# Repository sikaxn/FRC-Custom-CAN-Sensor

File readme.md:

## IronMaple ESP32‐FRC‐devkit sponsored by JLCPCB

If you are looking for IronMaple ESP32‐FRC‐devkit resources, please switch branch to dev-board.

Code, CAD models: https://github.com/sikaxn/FRC-Custom-CAN-Sensor/tree/dev-board/pcb

Manual: https://github.com/sikaxn/FRC-Custom-CAN-Sensor/wiki/800.-IronMaple-ESP32%E2%80%90FRC%E2%80%90devkit-Manual

Design file: https://oshwlab.com/sikaxn/seal-v2-dev-board

Factory test code: https://studenttechsupport.com/customcanespfw/factory/

## Firmware tbd fix

### Addressable LED

1. Allow change number of pixel over CAN **DONE**
2. offline detection on roborio driver **DONE**

### Battery Tracking

1. Indicator Task that use IM dev board RGB LED **DONE**
2. Better CAN protocol - Allow writing energy form roboRIO by user **DONE**
3. Better CAN protocol - Allow user to trigger tag rescan over CAN **DONE**
4. Better CAN protocol - More status feedback from ESP32 (tag write error) **DONE**
5. Better CAN protocol - Empty message upon startup **DONE**
6. Allow change CAN Device Number using web tool **DONE**
7. APP improvment - init new serial number follow BEST protocol (or disable this in setting)
8. APP improvment - App should not be set as default NFC app on Android

### IM ESP Devkit demo 

1. Bugfix - Change CAN Device Number using web tool currently not working. **DONE**
2. Maybe merge Addressable LED with it.

### Battery Tracking + addressable LED combined firmware

1. New firmware that combine those two together. **DONE**

# Custom CAN sensor with roboRIO

Please also check out the WiKi section for more documentation!

https://github.com/sikaxn/FRC-Custom-CAN-Sensor/wiki

# Some resources in another branch

This repo need some cleanup. Will do later.

https://github.com/sikaxn/FRC-Custom-CAN-Sensor/tree/dev-board

## IronMaple ESP32‐FRC‐devkit sponsored by JLCPCB

If you are looking for IronMaple ESP32‐FRC‐devkit resources, please switch branch to dev-board.

Code, CAD models: https://github.com/sikaxn/FRC-Custom-CAN-Sensor/tree/dev-board/pcb

Manual: https://github.com/sikaxn/FRC-Custom-CAN-Sensor/wiki/800.-IronMaple-ESP32%E2%80%90FRC%E2%80%90devkit-Manual

Design file: https://oshwlab.com/sikaxn/seal-v2-dev-board

Factory test code: https://studenttechsupport.com/customcanespfw/factory/

## Web firmware flasher

Pre built ESP32 firmware for Battery RFID Tracker and Addressable LED Controller. Just Chrome, USB and flash.

https://studenttechsupport.com/customcanespfw/

Web flasher source code: https://github.com/sikaxn/sikaxn.github.io/tree/master/customcanespfw

## ChiefDelphi Thread
https://www.chiefdelphi.com/t/custom-can-sensor-some-good-progress/501764

## Video

Potentiometer analog input
https://www.youtube.com/watch?v=bEm6USGRP-E

LED (pin 13) digital output
https://www.youtube.com/shorts/q937u09llhw

roboRIO heartbeat (look at the LED blinking while enabled)
https://www.youtube.com/shorts/c1ieu9o8Lzo

## ⚠️ Disclaimer

This project is **for demo and under work**. Faulty CAN frame could bring entire CAN bus down. 

This project use **AI generated content**. 

---
# What's in this repository:

1. [Arduino Mega] Digital Analog bi-directional ([Docs](Arduino/readme.md) / [Arduino Firmware](Arduino/Digital_Analog/) / [roboRIO](roboRIO/can-test/) / [RIO Simulator](scripts/ADrioSIm.py))
2. [Arduino Mega] REV Colour sensor  ([Docs](Arduino/readme.md) / [Arduino Firmware](Arduino/REVColourSensorV3/) / [roboRIO](roboRIO/can-test/)) (this share the same roboRIO code with the first one)
3. [Arduino Mega] LCD Screen  ([Arduino Firmware](Arduino/LCD/) / [roboRIO](roboRIO/can-LCD/) / [RIO Simulator](scripts/LCDSendRIOSIM.py))
4. **NOT FRC LEGAL** [ESP32] Robomaster motor gateway (dual CAN on ESP32)  ([Arduino Firmware](Arduino/RM_stuff/) / [roboRIO](roboRIO/djimotor/))
5. **NOT FRC LEGAL** Robomaster DT7 Remote on CAN  ([Arduino Firmware](Arduino/RM_stuff/) / [roboRIO](roboRIO/dt7/))
6. [ESP32] Battery Tracking System ([Arduino Firmware](Arduino/Battery_Tracking/batteryReaderAutoPD/) / [roboRIO](roboRIO/batteryReader/) / [Android APP](https://github.com/sikaxn/FRC-RFID-Battery-Reader) / [Docs](Arduino/Battery_Tracking/readme.md))
7. [ESP32] ToF using 4 VL53L1X ([Docs](Arduino/ToF/readme.md) / [Arduino Firmware](Arduino/ToF/laserCANx4/) / [roboRIO](roboRIO/ToF/) / [UITool](scripts/ToFReaderROI.py) / [ROI Calculator Tool](scripts/TofRIOCalc.py))
8. [ESP32] Addressable LED Controller ([Arduino Firmware](Arduino/addressableLED/) / [roboRIO](roboRIO/addressableLED/))
9. [ESP32] Battery Tracking ([Arduino Firmware](Arduino/Battery_Tracking/) / [roboRIO](roboRIO/batteryReaderNew/)) / [Docs](https://github.com/sikaxn/FRC-Custom-CAN-Sensor/wiki/900.-IronMaple-RFID-Battery-Tracking-Solution)
10. [ESP32] Battery Tracking LF ([Arduino Firmware](Arduino/Battery_Tracking_LF/) / [roboRIO](roboRIO/batteryReaderLF/)) / [Docs](Arduino/Battery_Tracking_LF/readme.md)
11. [ESP32] REV and Andymark Colour sensor ([Arduino Firmware](Arduino/REVAMColourSensor/) / [roboRIO](roboRIO/andymarkColourSensor/)) / [Docs](https://github.com/sikaxn/FRC-Custom-CAN-Sensor/wiki/920.-REV---Andymark-Colour-sensor-to-CAN-interface)

---

# Important reminder of ESP32 radio:

Per FRC Game Manual (2025) R707 and E301, Wi-Fi radio should not be used within competition area and Bluetooth radio should not be used if robot is competing on the field. As for now, none of the code utilizing ESP32 have any wireless capability. However, if further update enabled this capability, the use of such device and software should be carefully planned and coordinated to stay in compliance with the game manual. 

---
## How FRC CAN bus works

The 'CAN ID' we talked about when setting up motor controllers (Spark, Kraken, PDP, etc) is a number from 0-63. This is not the CAN identifier (message ID) used in CAN data layer. FRC Use a very specific scheme outlined in FRC CAN specification to convert certain information to CAN identifier. All device connected to roboRIO must follow this scheme when determine what ID to send data to and read form.

https://docs.wpilib.org/en/stable/docs/software/can-devices/can-addressing.html#requirements-for-frc-can-nodes

CAN identifier is calculated from device ID (device type ID), manufacturer ID, API ID (in the documentation it talked about API Class and Index but doesn't matter and it is just a suggestion. Each device will have its unique API ID designed for its use) and device number (0-63 as the traditional 'CAN ID' we talked about in FRC). 

You must generate your CAN identifier (message ID) using this very specific way. A device will have multiple CAN message sent to and from roboRIO (and possibly to other non-roboRIO device). These different messages will share the same device type ID, manufacturer ID and device number. API ID will change based on use. 

---
## Update

1. REVCOlourSensorV3 Arduino sketch has been updated to do conversion in code. In addition, rm_dt7 is added to handle Robomaster / DJI DT7 Remote with DR16. This is not legal to use in FRC. However you could still take a look at these conversion. 

```
// === CAN Constants ===
#define DEVICE_TYPE_ID        0x0A  //DONOT CHANGE
#define MANUFACTURER_ID  0x08  //DONOT CHANGE
#define DEVICE_NUMBER    33  // Device Number 0-63
#define STATUS_API_ID        0x180
#define COLOR_SENSOR_API_ID  0x184
#define CONTROL_API_ID       0x190
#define HEARTBEAT_ID         0x01011840

uint32_t makeCANMsgID(uint8_t deviceID, uint8_t manufacturerID, uint16_t apiID, uint8_t deviceNumber) {
  return ((uint32_t)(deviceID & 0xFF) << 24) |
         ((uint32_t)(manufacturerID & 0xFF) << 16) |
         ((uint32_t)(apiID & 0x3FF) << 6) |
         (deviceNumber & 0x3F);
}
```
2. An ID converter script is added. see below for usage.

3. DO NOT change DEVICE_TYPE_ID and MANUFACTURER_ID as this will result roboRIO code stop working. 

---

---

## **Message ID Generator GUI Tool**

A minimal Tkinter application for converting between FRC 29-bit CAN IDs and their four fields.

## **CANDbg Message Viewer tool**

A minimal Tkinter application viewing CAN messages using python-can.

Support Ctrl + C to copy message and roboRIO heartbeat decoding.

---

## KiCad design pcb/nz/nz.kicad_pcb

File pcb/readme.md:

# IronMaple ESP32-FRC-devkit

Please visit https://oshwlab.com/sikaxn/seal-v2-dev-board

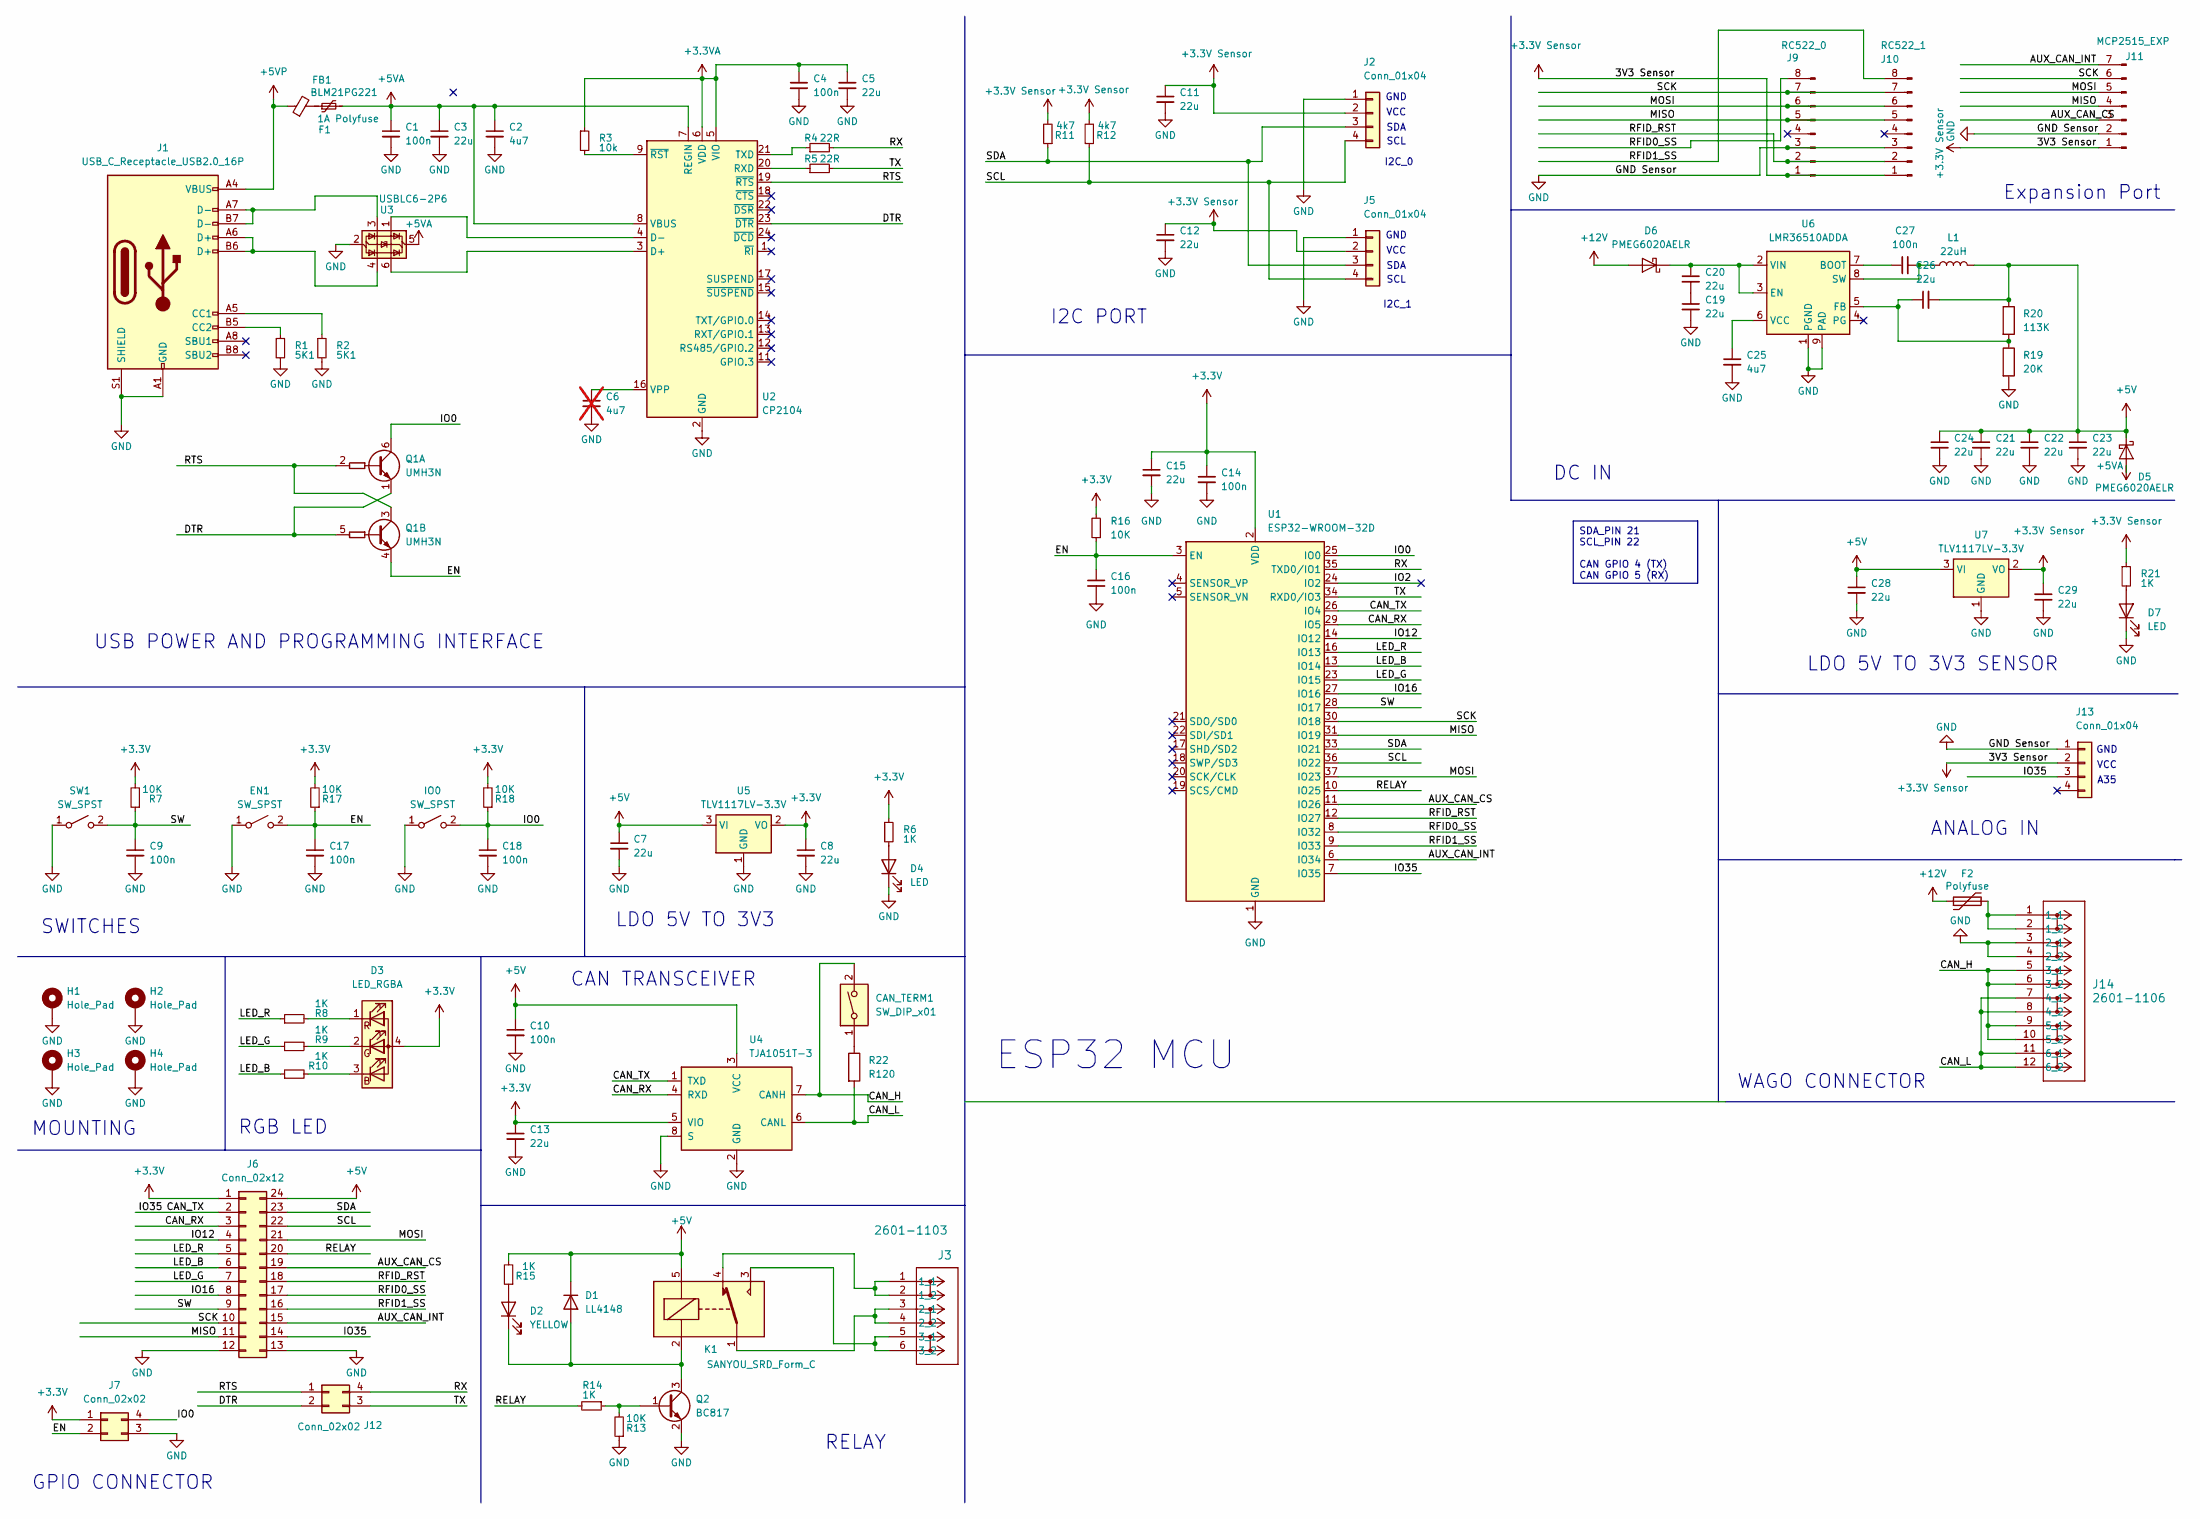
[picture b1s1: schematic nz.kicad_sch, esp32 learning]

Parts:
C1, C4, C9, C10, C14, C16, C17, C18, C27: 100n; C_01005_0402Metric
C2, C25: 4u7; C_01005_0402Metric
C3, C5, C7, C8, C11, C12, C13, C15, C19, C20, C21, C22, C23, C24, C26, C28, C29: 22u; C_01005_0402Metric
C6: 4u7; C_01005_0402Metric; not fitted
CAN_TERM1: SW_DIP_x01; SW_DIP_SPSTx01_Slide_6.7x4.1mm_W6.73mm_P2.54mm_LowProfile_J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
D1: LL4148; D_MiniMELF
D2: YELLOW; LED_0201_0603Metric
D3: LED_RGBA; LED_RGB_Wuerth-PLCC4_3.2x2.8mm_150141M173100
D4, D7: LED; LED_0201_0603Metric
D5, D6: PMEG6020AELR; Nexperia_CFP3_SOD-123W
EN1: SW_SPST; SW_Push_1P1T_NO_6x6mm_H9.5mm
F1: 1A Polyfuse; Fuse_1206_3216Metric_Pad1.42x1.75mm_HandSolder
F2: Polyfuse; Fuse_1206_3216Metric_Pad1.42x1.75mm_HandSolder
FB1: BLM21PG221; L_0603_1608Metric_Pad1.05x0.95mm_HandSolder
H1, H2, H3, H4: Hole_Pad; MountingHole_3.2mm_M3_Pad_Via
IO0: SW_SPST; SW_Push_1P1T_NO_6x6mm_H9.5mm
J1: USB_C_Receptacle_USB2.0_16P; USB_C_Receptacle_HRO_TYPE-C-31-M-12
J2, J5, J13: Conn_01x04; PinHeader_1x04_P1.00mm_Vertical
J3: 2601-1103; CONN3_2601-1103_WAG
J6: Conn_02x12; PinHeader_2x12_P1.00mm_Vertical
J7, J12: Conn_02x02; PinHeader_2x02_P1.00mm_Vertical
J9: RC522_0; PinHeader_1x08_P1.00mm_Vertical
J10: RC522_1; PinHeader_1x08_P1.00mm_Vertical
J11: MCP2515_EXP; PinHeader_1x07_P1.00mm_Vertical
J14: 2601-1106; CONN6_2601-1106_WAG
K1: SANYOU_SRD_Form_C; Relay_SPDT_SANYOU_SRD_Series_Form_C
L1: 22uH; L_1008_2520Metric
Q1: UMH3N; SOT-363_SC-70-6
Q2: BC817; SOT-23
R1, R2: 5K1; R_0402_1005Metric
R3: 10k; R_0402_1005Metric
R4, R5: 22R; R_0402_1005Metric
R6, R8, R9, R10, R14, R15, R21: 1K; R_0402_1005Metric
R7, R13, R16, R17, R18: 10K; R_0402_1005Metric
R11, R12: 4k7; R_0402_1005Metric
R19: 20K; R_0402_1005Metric
R20: 113K; R_0402_1005Metric
R22: R120; R_0402_1005Metric
SW1: SW_SPST; SW_Push_1P1T_NO_6x6mm_H9.5mm
U1: ESP32-WROOM-32D; ESP32-WROOM-32D-3d
U2: CP2104; QFN-24-1EP_4x4mm_P0.5mm_EP2.6x2.6mm
U3: USBLC6-2P6; SOT-666
U4: TJA1051T-3; SOIC-8_3.9x4.9mm_P1.27mm
U5, U7: TLV1117LV-3.3V; SOT-223-3_TabPin2
U6: LMR36510ADDA; Texas_HTSOP-8-1EP_3.9x4.9mm_P1.27mm_EP2.95x4.9mm_Mask2.4x3.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

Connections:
+3.3V: C8.1, C13.1, C14.1, C15.1, D3.4 (A), J6.1, J7.1, R6.1, R7.2, R16.2, R17.2, R18.2, U1.2 (VDD), U4.5 (VIO), U5.2 (VO)
+3.3V Sensor: C11.1, C12.1, C29.1, J2.2, J5.2, J9.1, J10.1, J11.1, J13.2, R11.2, R12.2, R21.1, U7.2 (VO)
+3.3VA: C4.1, C5.1, R3.1, U2.5 (VIO), U2.6 (VDD)
+5V: C7.1, C10.1, C21.1, C22.1, C23.1, C24.1, C26.2, C28.1, D1.1 (K), D5.1 (K), J6.24, K1.5, L1.2, R15.2, R20.1, U4.3 (VCC), U5.3 (VI), U7.3 (VI)
+5VA: C1.1, C2.1, C3.1, D5.2 (A), F1.2, U2.7 (REGIN), U2.8 (VBUS), U3.5 (VBUS)
+5VP: FB1.1, J1.A4 (VBUS), J1.A9 (VBUS), J1.B4 (VBUS), J1.B9 (VBUS)
+12V: D6.2 (A), F2.1
/AUX_CAN_CS: J6.19, J11.3, U1.11 (IO26)
/AUX_CAN_INT: J6.15, J11.7, U1.6 (IO34)
/CAN_H: CAN_TERM1.2, J14.5 (3_1), J14.6 (3_2), J14.9 (5_1), J14.10 (5_2), U4.7 (CANH)
/CAN_L: J14.7 (4_1), J14.8 (4_2), J14.11 (6_1), J14.12 (6_2), R22.2, U4.6 (CANL)
/CAN_RX: J6.3, U1.29 (IO5), U4.4 (RXD)
/CAN_TX: J6.2, J6.14, J13.3, U1.7 (IO35), U1.26 (IO4), U4.1 (TXD)
/DTR: J12.2, Q1.1 (E1), Q1.5 (B2), U2.23 (~DTR)
/EN: C16.1, C17.1, EN1.2 (B), J7.2, Q1.4 (E2), R16.1, R17.1, U1.3 (EN)
/IO0: C18.1, IO0.2 (B), J7.4, Q1.6 (C1), R18.1, U1.25 (IO0)
/IO2: U1.24 (IO2)
/IO12: J6.4, U1.14 (IO12)
/IO16: J6.8, U1.27 (IO16)
/LED_B: J6.6, R10.1, U1.13 (IO14)
/LED_G: J6.7, R9.1, U1.23 (IO15)
/LED_R: J6.5, R8.1, U1.16 (IO13)
/MISO: J6.11, J9.5, J10.5, J11.4, U1.31 (IO19)
/MOSI: J6.21, J9.6, J10.6, J11.5, U1.37 (IO23)
/RELAY: J6.20, R14.2, U1.10 (IO25)
/RFID0_SS: J6.17, J9.8, U1.8 (IO32)
/RFID1_SS: J6.16, J10.8, U1.9 (IO33)
/RFID_RST: J6.18, J9.2, J10.2, U1.12 (IO27)
/RTS: J12.1, Q1.2 (B1), Q1.3 (C2), U2.19 (~RTS)
/RX: J12.4, R4.2, U1.35 (TXD0/IO1)
/SCK: J6.10, J9.7, J10.7, J11.6, U1.30 (IO18)
/SCL: J2.4, J5.4, J6.22, R12.1, U1.36 (IO22)
/SDA: J2.3, J5.3, J6.23, R11.1, U1.33 (IO21)
/SW: C9.1, J6.9, R7.1, SW1.2 (B), U1.28 (IO17)
/TX: J12.3, R5.2, U1.34 (RXD0/IO3)
GND: C1.2, C2.2, C3.2, C4.2, C5.2, C6.2, C7.2, C8.2, C9.2, C10.2, C11.2, C12.2, C13.2, C14.2, C15.2, C16.2, C17.2, C18.2, C19.2, C21.2, C22.2, C23.2, C24.2, C25.2, C28.2, C29.2, D4.1 (K), D7.1 (K), EN1.1 (A), H1.1, H2.1, H3.1, H4.1, IO0.1 (A), J1.A1 (GND), J1.A12 (GND), J1.B1 (GND), J1.B12 (GND), J1.S1 (SHIELD), J2.1, J5.1, J6.12, J6.13, J7.3, J9.3, J10.3, J11.2, J13.1, J14.3 (2_1), J14.4 (2_2), Q2.2 (E), R1.2, R2.2, R13.1, R19.2, SW1.1 (A), U1.1 (GND), U1.15 (GND), U1.38 (GND), U1.39 (GND), U2.2 (GND), U2.25 (GND), U3.2 (GND), U4.2 (GND), U4.8 (S), U5.1 (GND), U6.1 (PGND), U6.9 (PAD), U7.1 (GND)
unnamed: C19.1, C20.2
unnamed: CAN_TERM1.1, R22.1
unnamed: D1.2 (A), D2.1 (K), K1.2, Q2.3 (C)
unnamed: D2.2 (A), R15.1
unnamed: D3.3 (BK), R10.2
unnamed: D3.2 (GK), R9.2
unnamed: D3.1 (RK), R8.2
unnamed: D4.2 (A), R6.2
unnamed: C20.1, D6.1 (K), U6.2 (VIN), U6.3 (EN)
unnamed: D7.2 (A), R21.2
unnamed: F1.1, FB1.2
unnamed: J1.A5 (CC1), R2.1
unnamed: J1.B5 (CC2), R1.1
unnamed: J1.A6 (D+), J1.B6 (D+), U3.4 (I/O2)
unnamed: J1.A7 (D-), J1.B7 (D-), U3.3 (I/O2)
unnamed: J3.1 (1_1), J3.2 (1_2), K1.4
unnamed: J3.3 (2_1), J3.4 (2_2), K1.1
unnamed: J3.5 (3_1), J3.6 (3_2), K1.3
unnamed: F2.2, J14.1 (1_1), J14.2 (1_2)
unnamed: Q2.1 (B), R13.2, R14.1
unnamed: U2.3 (D+), U3.6 (I/O1)
unnamed: U2.4 (D-), U3.1 (I/O1)
unnamed: R5.1, U2.20 (RXD)
unnamed: R4.1, U2.21 (TXD)
unnamed: C6.1, U2.16 (VPP)
unnamed: R3.2, U2.9 (~RST)
unnamed: C27.1, U6.7 (BOOT)
unnamed: C26.1, R19.1, R20.2, U6.5 (FB)
unnamed: C27.2, L1.1, U6.8 (SW)
unnamed: C25.1, U6.6 (VCC)

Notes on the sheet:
SDA_PIN 21 SCL_PIN 22 CAN GPIO 4 (TX) CAN GPIO 5 (RX)
LDO 5V TO 3V3 SENSOR
CAN TRANSCEIVER
RELAY
I2C_1
LDO 5V TO 3V3
GND
VCC
I2C PORT
MOUNTING
ESP32 MCU
RGB LED
A35
WAGO CONNECTOR
GPIO CONNECTOR
I2C_0
ANALOG IN
SDA
DC IN
SWITCHES
USB POWER AND PROGRAMMING INTERFACE
SCL
Expansion Port

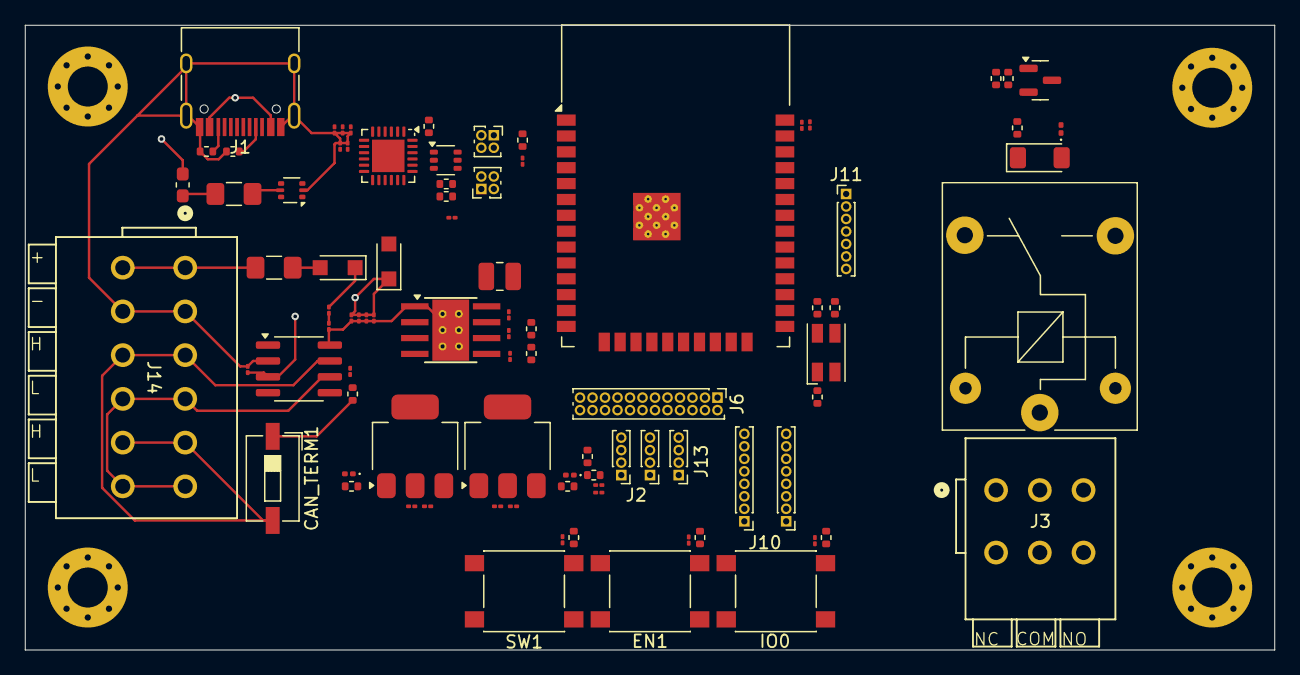
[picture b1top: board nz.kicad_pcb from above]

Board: 6 copper layers, 100.0 x 50.0 mm, 92 parts (0 on the bottom side), 65 nets.

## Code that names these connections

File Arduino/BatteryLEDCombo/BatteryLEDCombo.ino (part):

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// ===============  HARDWARE DEFINITIONS  ============
// ==================================================
#define RST_PIN        22
#define CAN_TX_PIN     GPIO_NUM_4
#define CAN_RX_PIN     GPIO_NUM_5

// RGB LED Pins
#define LED_R 15
#define LED_G 13
#define LED_B 14
#define RELAY_PIN 25
#define LED_TOGGLE_BTN_PIN 17

// Addressable LED Strip
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QueueHandle_t canRxQueue;

void setup() {
  pinMode(LED_R, OUTPUT);
  pinMode(LED_B, OUTPUT);
  pinMode(LED_G, OUTPUT);
  pinMode(RELAY_PIN, OUTPUT);
  digitalWrite(RELAY_PIN, LOW);
  pinMode(LED_TOGGLE_BTN_PIN, INPUT_PULLUP);

  Serial.begin(115200);
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  // === CAN (TWAI) Configuration ===
  twai_general_config_t g_config = {
    .mode = TWAI_MODE_NORMAL,
    .tx_io = CAN_TX_PIN,
    .rx_io = CAN_RX_PIN,
    .clkout_io = TWAI_IO_UNUSED,
    .bus_off_io = TWAI_IO_UNUSED,
    .tx_queue_len = 5,
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  bool lastBtn = digitalRead(0);
  bool lastToggleBtn = digitalRead(LED_TOGGLE_BTN_PIN);
  for (;;) {
    digitalWrite(RELAY_PIN, (localLedEnabled && canOnOff) ? HIGH : LOW);
    bool toggleBtn = digitalRead(LED_TOGGLE_BTN_PIN);
    if (lastToggleBtn == HIGH && toggleBtn == LOW) {
      localLedEnabled = !localLedEnabled;
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
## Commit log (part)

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2025-05-14 init commit
2025-05-14 fixed can RX issue on arduino
2025-05-14 updated doc
2025-05-14 bug fix and have arduino listen roborio heartbeat
2025-05-15 added support for rev colour sensor v3 on arduino
2025-05-16 fix an issue where if it is very bright white colour sensor would disconnect
2025-05-18 ID conversion tool
2025-05-18 id conversion update
2025-05-18 added dt7 decoding
2025-05-23 eeee
2025-05-23 dt7 explain
2025-05-26 add support to dji motor
2025-05-26 improved dji motor api
2025-05-29 add LCD
2025-05-30 add lcd java
2025-05-30 add battery example
2025-05-30 doc update and cleaning folder structure
2025-05-30 make repository cleaner
2025-06-05 api improvement before moving on to CAN
2025-06-06 add roborio lib
2025-06-06 bugfix
2025-06-06 battery manager task added
2025-06-06 docs update
2025-06-06 folder name change
2025-06-06 img update
2025-06-07 now use UTC on json
2025-06-07 utc fix
2025-06-09 reader holder img
2025-06-10 pd auto discovery test
2025-06-11 always use pd voltage first
2025-06-11 energy calculation updated
2025-06-11 comment clean up
2025-06-13 add tof
2025-06-13 uodate readme
2025-06-13 added roi ui tool
2025-06-13 pushing the limit...
2025-06-14 revert some mistake
2025-06-14 ToF Roborio driver started
2025-06-17 added pcb
2025-06-18 ipdate
2025-06-18 (trying) to fix roi
2025-06-18 update roborio driver
2025-06-18 clean up dir
2025-06-18 add ToF readme
2025-06-19 update doc
2025-06-22 started addressable led
2025-06-22 update led
2025-06-22 script update
2025-06-23 add some riosim for led
2025-06-23 add roborio driver
2025-06-23 make pattern even slower
2025-06-23 doc update
2025-06-23 supress print
2025-06-23 rainbow stript don't need moderefresh
2025-06-23 doc update and remove unused function
2025-06-23 comment update
2025-06-25 added dbglcd
2025-06-26 fixing a lot of s***
2025-06-26 heartbeat decoding fixed
2025-06-26 added packet reader
2025-06-26 safer memory (maybe)
2025-06-26 some not so neat workarond
2025-06-26 more memory issue fixed???
2025-06-27 try to add debug ui
2025-06-27 make ui betert
2025-06-27 ui scroll fix
2025-06-27 no more Matryoshka in dbg btn container
2025-06-27 fixing a very s***** bug.
2025-06-27 roll back
2025-06-28 update espwebtool link
2025-06-29 drawing added
2025-06-29 fix image overlap
2025-06-30 update image again
2025-07-13 add some more chart
2025-07-13 update chart
2025-07-13 add a feature to save CAN ID to EEPROM and set CAN ID via serial port for addressable LED
2025-07-13 added web CAN ID tool
2025-07-14 update pcb
2025-07-16 add cad
2025-08-09 change some io for dev board
2025-08-09 web tool build cmd
2025-08-09 add factory
2025-09-05 dev board update
2025-09-06 pcb roborio move
2025-09-06 update to give adc readout thru nt
2025-09-06 cal bugfix
2025-09-08 change setpoint
2025-09-08 clean up
2025-09-08 updatefactory
2025-09-08 update factory fw instruction
2025-09-08 added rev colour sensor
2025-09-16 added round 2 production file
2025-09-16 add cad resources
2025-09-16 remove cache
2025-09-16 add demo backplate stl
2025-10-04 added some imu
2025-10-16 add a dummy ctre motor to troubleshoot ctre related issue
2025-10-17 demo update for the code
2025-10-20 Update README with branch resources and cleanup note
    Added a section for resources in another branch and noted cleanup.
2025-11-03 new CAN stack for batteryReaderPD (Not Ready Yet Do Not use on comp)
2025-11-04 (some update but still not ready,
2025-11-04 preview battery fw java api update
2025-11-04 elimiate need for period call by user
2025-11-04 run faster for global data task
2025-11-04 added esp offline notification and some console print
2025-11-04 error handling for rio
2025-11-05 update led and CAN bus off recover
2025-11-05 write fail led indicator
2025-11-05 better wording for java auth fail / write fail
2025-11-05 update LF reader
2025-11-05 added LF
2025-11-05 added lf drawing
2025-11-06 Add compatibility warning to readme
    Added compatibility warning regarding system limitations and technology differences.
2025-11-06 allow device number to be changed via serial for batterycan
2025-11-07 Update ESP32 Online Flasher link in readme
2025-11-10 Add initial readme with a note on issues
2025-11-10 move away the imu project so it does not create confusion
2025-11-17 improved can logic for rio batterycan driver
2025-11-20 added RTC
2025-11-26 add am sensor test
2025-11-27 add rev colour sensor esp32
2025-12-01 add am colour sensor
2025-12-01 add am colour rio code
2025-12-01 offline bugfix for rio driver
2025-12-05 bump some rio project to 2026
2025-12-05 move autopd preview to formal
2025-12-19 Enhance readme with Getting Started and wiring info
    Added a 'Getting Started' section and updated wiring information.
2025-12-21 add combo firmware
2025-12-21 update readme and riosim led to default can id for quick debug
2025-12-23 can device number bugfix
2025-12-24 added im assistant
2025-12-24 im assistant update
2025-12-25 im asst work
2025-12-25 menu bar
2025-12-25 assistant wrk
2025-12-25 im assistant update and prerelease
2026-01-04 combining...
2026-01-04 readme
2026-01-08 add battery reader on IM Assistant
2026-01-08 tag tool update
2026-01-09 IM asst battery reader update
2026-01-09 print bugfix
2026-01-09 bugfix more
2026-01-10 demo fw 2026 rio driver
2026-01-12 battery led combo polished
2026-01-12 added combo firmware drawing
2026-01-12 added 2 new pattern
2026-01-13 led pattern bugfix
2026-01-13 bugfix and some more pattern.
2026-01-13 change startup sequence for led.
2026-01-14 relay and button function added
2026-01-14 slight improvement and doc update
2026-01-14 local blackoff added
2026-01-21 start some update to led standalone
2026-01-21 add test bot code
2026-01-27 rfid disable toggle
2026-01-28 secondary colour support
2026-01-28 update arcade test
2026-01-29 add led simulator
2026-01-30 rename all device_id to device_type_id, clean up repo.
2026-02-02 CANdbg V2
2026-02-02 updated battery led protocol
2026-02-02 add api index class support
2026-02-03 ui tweak
2026-02-03 more ui improvement
2026-02-03 more ui...
2026-02-04 add imgui version
2026-02-26 clean up repo
2026-06-23 add c3 board
2026-06-30 esp32 2027 fw
2026-06-30 improve rainbow
2026-06-30 enable led
2026-06-30 driver update
